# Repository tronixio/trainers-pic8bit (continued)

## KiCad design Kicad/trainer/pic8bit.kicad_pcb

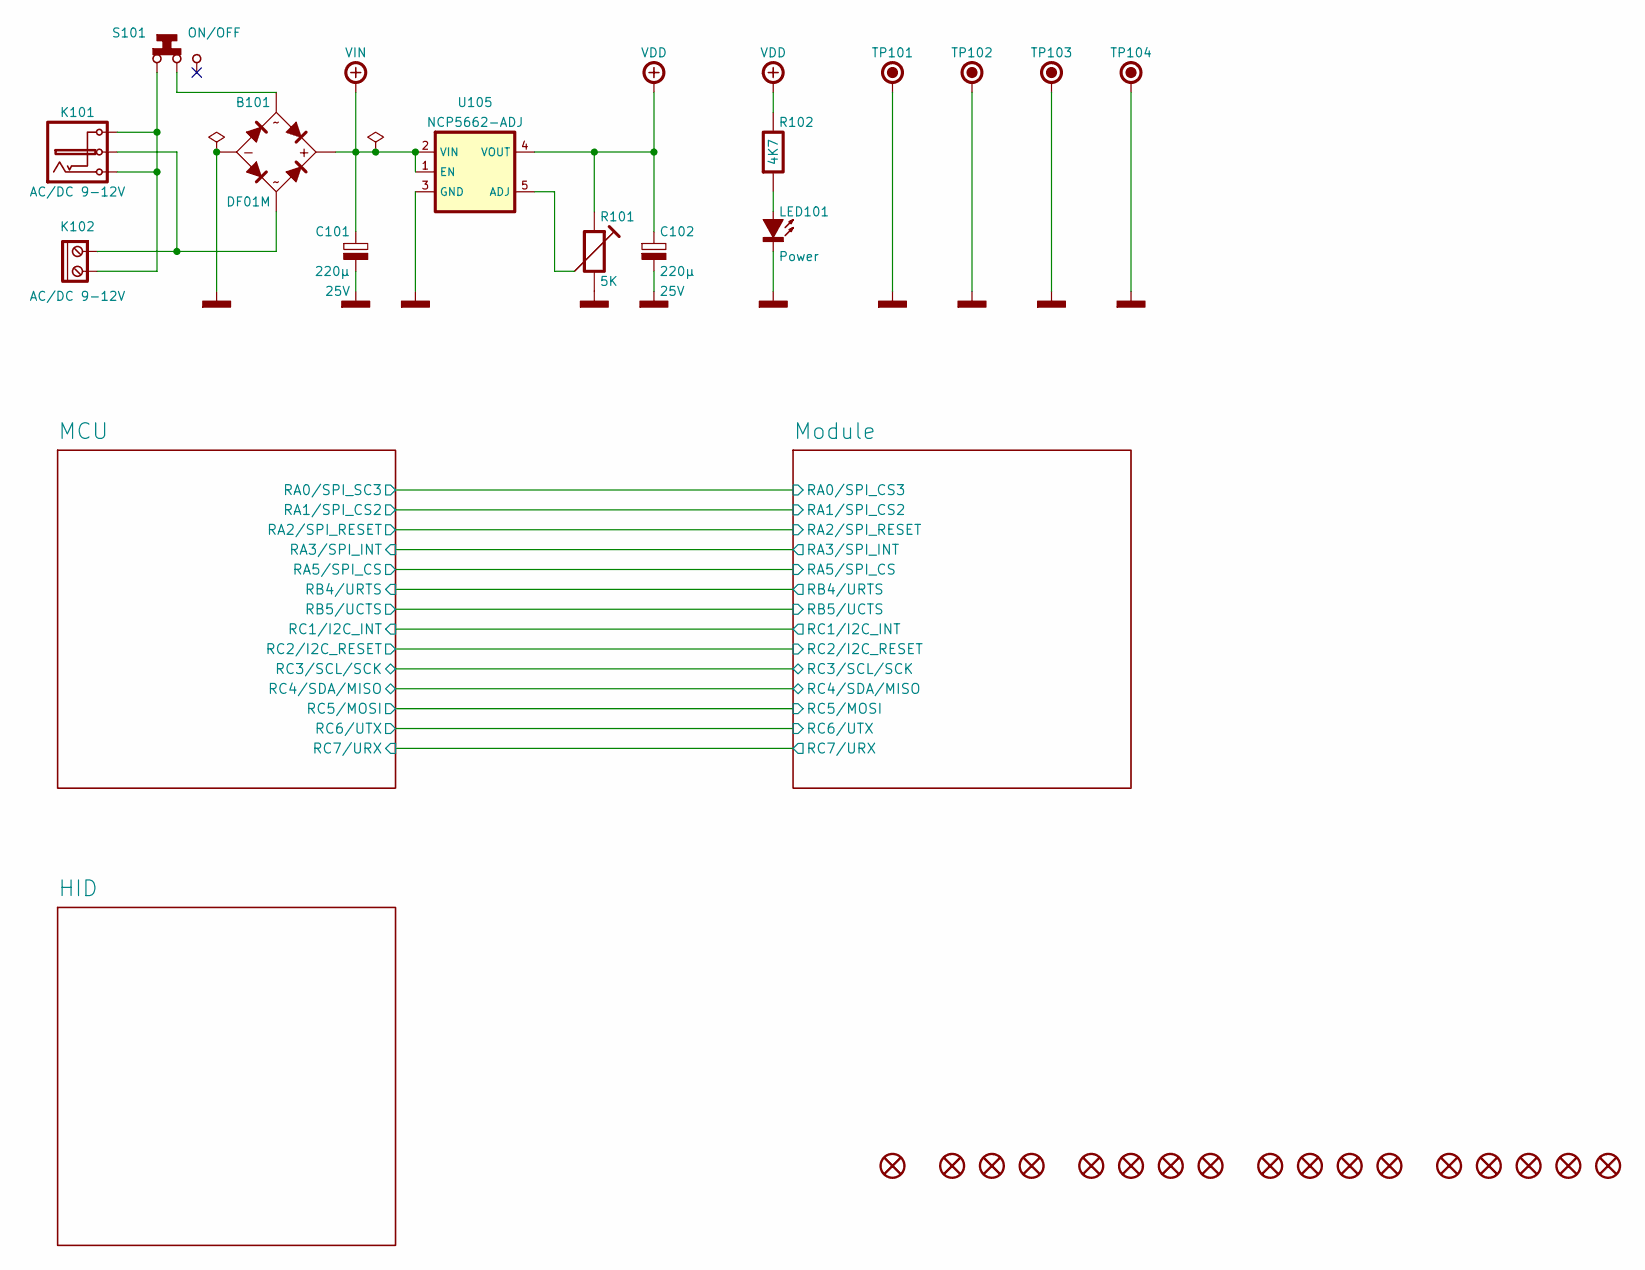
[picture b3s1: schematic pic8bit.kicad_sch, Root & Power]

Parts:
B101: DF01M; Mouser 512-DF01M
C101, C102: 220µ; CAPACITOR-ELECTROLYTIC-RADIAL-080-115-035; Voltage 25V; Tolerance 20%; Mouser 647-UVZ1E221MPD
H101, H102, H103, H104: HARWIN-JUMPER-0254-14MM-BLACK; HARWIN-M20-7680-7683; Mouser 855-M7682
JP101: HARWIN-JUMPER-0254-06MM-BLACK; HARWIN-M20-7580-7583; Mouser 855-M7582
JP102, JP103: HARWIN-JUMPER-0254-06MM-RED; HARWIN-M20-7580-7583; Mouser 855-M7581
K101: AC/DC 9-12V; SAMESKY-PJ-102AH; Mouser 490-PJ-102AH
K102: AC/DC 9-12V; SAMESKY-TB006-508-02BE; Mouser 490-TB006-508-02BE
K103: PE-450-4X6X-BLACK; PE-450-4X6X; Mouser 450-476
LED101: Power; LED-TH-ROUND-05MM; Mouser 604-WP7113ID
R101: 5K; TRIMMER-64W; Tolerance 10%; Mouser 594-64W502
R102: 4K7; RESISTOR-TH-1016; Tolerance 5%; Mouser 594-SFR2500004701JR5
S101: ON/OFF; CK-1101M2; Mouser 611-1101M2S3CQE2
TP101, TP102, TP103: GND; KEYSTONE-5006; Mouser 534-5006
TP104: GND; KEYSTONE-2000-3; Mouser 534-2000-3
U101, U102, U103, U104: KEYSTONE-24283; Mouser 534-24283
U105: NCP5662-ADJ; TO-263-5-TABPIN3; Mouser 863-NCP5662DSADJR4G
X101, X102, X103, X104, X105: 3M-SJ5376; Mouser 517-SJ5376

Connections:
unnamed: B101.3, K101.1, K102.1
unnamed: B101.4, S101.2
unnamed: K101.2, K101.3, K102.2, S101.1
unnamed: LED101.2 (A), R102.2
unnamed: R101.2, U105.5 (ADJ)
POWER-GND: B101.2, C101.2, C102.2, LED101.1 (C), R101.1, TP101.1, TP102.1, TP103.1, TP104.1, U105.3 (GND); also elsewhere on the board
POWER-VDD: C102.1, R101.3, R102.1, U105.4 (VOUT); also elsewhere on the board
POWER-VIN: B101.1, C101.1, U105.1 (EN), U105.2 (VIN); also elsewhere on the board

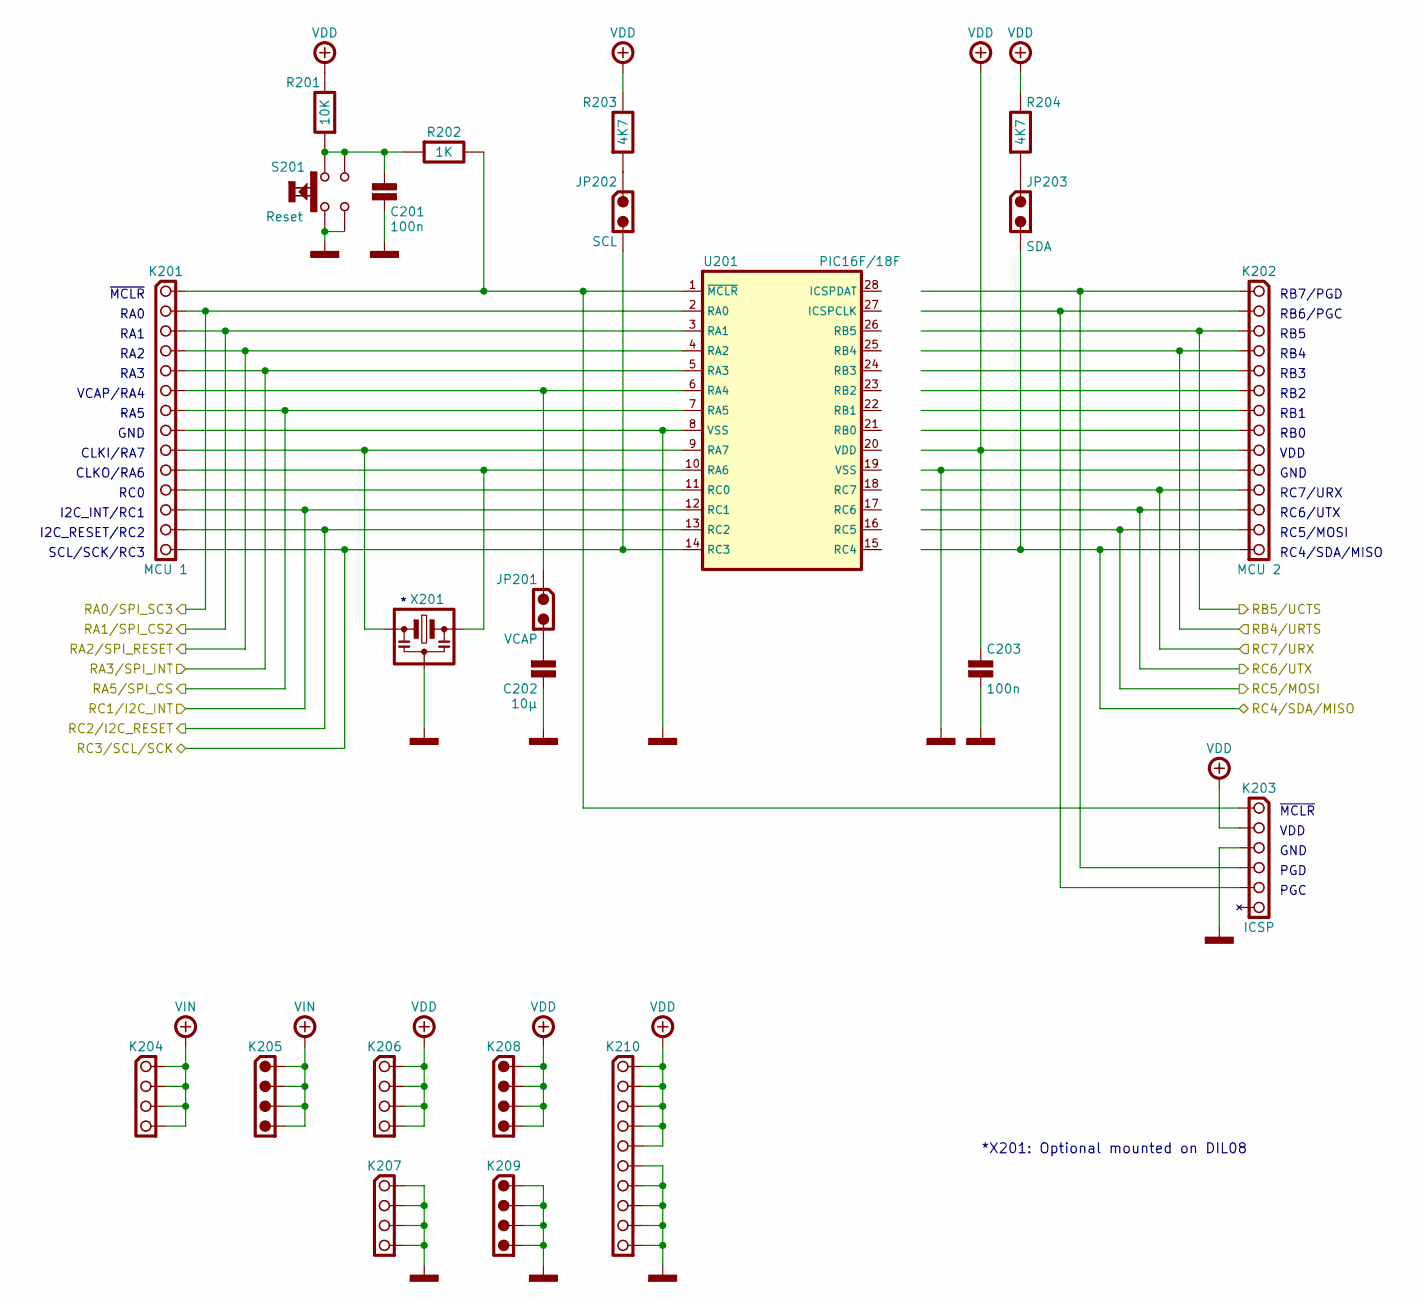
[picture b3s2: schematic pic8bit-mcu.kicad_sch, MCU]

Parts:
C201, C203: 100n; KEMET-C315; Tolerance 20%; Voltage 50V; Mouser 80-C315C104M5U
C202: 10µ; KEMET-C322; Tolerance 10%; Voltage 25V; Mouser 80-C322C106K3R
JP201: VCAP; HARWIN-M20-975024x; Mouser 855-M20-975024
JP202: SCL; HARWIN-M20-999024x; Mouser 855-M20-999024
JP203: SDA; HARWIN-M20-999024x; Mouser 855-M20-999024
K201: MCU 1; HARWIN-M20-782144x; Mouser 855-M20-782144
K202: MCU 2; HARWIN-M20-782144x; Mouser 855-M20-782144
K203: ICSP; SAMTEC-SSW-106-02-T-S-RA; Mouser 200-SSW10602TSRA
K204: VIN; HARWIN-M20-782044x; Mouser 855-M20-782044
K205: VIN; HARWIN-M20-999044x; Mouser 855-M20-999044
K206: VDD; HARWIN-M20-782044x; Mouser 855-M20-782044
K207: GND; HARWIN-M20-782044x; Mouser 855-M20-782044
K208: VDD; HARWIN-M20-999044x; Mouser 855-M20-999044
K209: GND; HARWIN-M20-999044x; Mouser 855-M20-999044
K210: VDD & GND; HARWIN-M20-782104x; Mouser 855-M20-782104
R201: 10K; RESISTOR-TH-1016; Tolerance 5%; Mouser 594-SFR2500001002JA5
R202: 1K; RESISTOR-TH-1016; Tolerance 5%; Mouser 594-SFR2500001001JR5
R203, R204: 4K7; RESISTOR-TH-1016; Tolerance 5%; Mouser 594-SFR2500004701JR5
S201: Reset; CK-KSA-TH; Mouser 611-KSA0M911LFT
U201: PIC16F/18F; DIP-28-W762; Mouser 579-PIC16F1778-I/SP
X201: XTAL-DIL08; DIP-08-W762-SOCKET; Mouser 575-144308

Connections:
/MCU/RA0/SPI_SC3: K201.2, U201.2 (RA0); also elsewhere on the board
/MCU/RA1/SPI_CS2: K201.3, U201.3 (RA1); also elsewhere on the board
/MCU/RA2/SPI_RESET: K201.4, U201.4 (RA2); also elsewhere on the board
/MCU/RA3/SPI_INT: K201.5, U201.5 (RA3); also elsewhere on the board
/MCU/RA5/SPI_CS: K201.7, U201.7 (RA5); also elsewhere on the board
/MCU/RB4/URTS: K202.4; also elsewhere on the board
/MCU/RB5/UCTS: K202.3; also elsewhere on the board
/MCU/RC1/I2C_INT: K201.12, U201.12 (RC1); also elsewhere on the board
/MCU/RC2/I2C_RESET: K201.13, U201.13 (RC2); also elsewhere on the board
/MCU/RC3/SCL/SCK: JP202.2, K201.14, U201.14 (RC3); also elsewhere on the board
/MCU/RC4/SDA/MISO: JP203.2, K202.14; also elsewhere on the board
/MCU/RC5/MOSI: K202.13; also elsewhere on the board
/MCU/RC6/UTX: K202.12; also elsewhere on the board
/MCU/RC7/URX: K202.11; also elsewhere on the board
unnamed: C201.1, R201.2, R202.2, S201.1, S201.2
unnamed: C202.1, JP201.2
unnamed: JP202.1, R203.2
unnamed: JP203.1, R204.2
unnamed: K201.1, K203.6 (~MCLR), R202.1, U201.1 (~MCLR)
unnamed: JP201.1, K201.6, U201.6 (RA4)
unnamed: K201.9, U201.9 (RA7), X201.3, X201.4
unnamed: K201.10, U201.10 (RA6), X201.5, X201.6
unnamed: K201.11, U201.11 (RC0)
unnamed: K202.1, K203.3 (PGD)
unnamed: K202.2, K203.2 (PGC)
POWER-GND: C201.2, C202.2, C203.2, K201.8, K202.10, K203.4 (GND), K207.1, K207.2, K207.3, K207.4, K209.1, K209.2, K209.3, K209.4, K210.6, K210.7, K210.8, K210.9, K210.10, S201.3, S201.4, U201.8 (VSS), X201.1, X201.2, X201.7, X201.8; also elsewhere on the board
POWER-VDD: C203.1, K202.9, K203.5 (VCC), K206.1, K206.2, K206.3, K206.4, K208.1, K208.2, K208.3, K208.4, K210.1, K210.2, K210.3, K210.4, K210.5, R201.1, R203.1, R204.1; also elsewhere on the board
POWER-VIN: K204.1, K204.2, K204.3, K204.4, K205.1, K205.2, K205.3, K205.4; also elsewhere on the board

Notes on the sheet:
RC6/UTX
VCAP/RA4
CLKI/RA7
VDD
PGC
RA3
RA0
RA2
RB6/PGC
RB5
*X201: Optional mounted on DIL08
RB7/PGD
~{MCLR}
GND
CLKO/RA6
PGD
RB4
RB2
RA1
RB3
RC5/MOSI
RA5
RB0
RC7/URX
RC4/SDA/MISO
I2C_INT/RC1
RC0
I2C_RESET/RC2
RB1
SCL/SCK/RC3

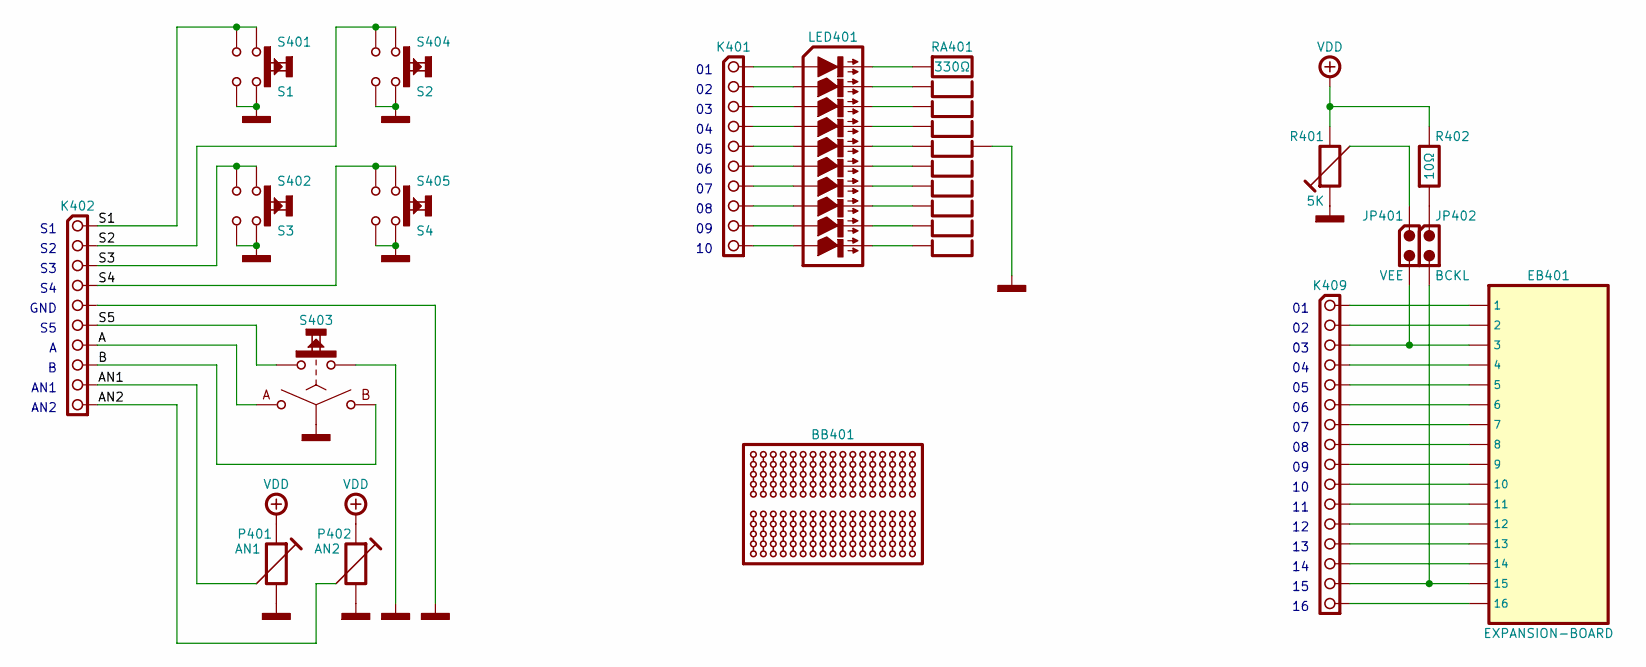
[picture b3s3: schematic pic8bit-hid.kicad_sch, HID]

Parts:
BB401: BREADBOARD-170; Mouser 854-BB170
EB401: EXPANSION-BOARD; TRONIXIO-EXPANSION-BOARD; Mouser 200-CES11601TS
JP401: VEE; HARWIN-M20-999024x; Mouser 855-M20-999024
JP402: BCKL; HARWIN-M20-999024x; Mouser 855-M20-999024
K401: LED ARRAY; HARWIN-M20-782104x; Mouser 855-M20-782104
K402: SWITCH, ENCODER & ANALOG; HARWIN-M20-782104x; Mouser 855-M20-782104
K409: EXPANSION BOARD; HARWIN-M20-782164x; Mouser 855-M20-782164
LED401: KINGBRIGHT-DC10EWA; KINGBRIGHT-DC; Mouser 604-DC-10EWA
P401: AN1; PIHER-PT10MV; Tolerance 20%; Mouser 531-PT10MV-10K
P402: AN2; PIHER-PT10MV; Tolerance 20%; Mouser 531-PT10MV-10K
R401: 5K; PIHER-PT10MV; Tolerance 20%; Mouser 531-PT10LV-5K
R402: 10Ω; RESISTOR-TH-1016; Tolerance 5%; Mouser 594-5043EM10R00J
RA401: 330Ω; BOURNS-4611X; Tolerance 2%; Mouser 652-4611X-1LF-330
S401: S1; CK-KSA-TH; Mouser 611-KSA0M911LFT
S402: S3; CK-KSA-TH; Mouser 611-KSA0M911LFT
S403: BOURNS-PEC12R-24DENTS; BOURNS-PEC12R-SWITCH; Mouser 652-PEC12R-4215F-S24
S404: S2; CK-KSA-TH; Mouser 611-KSA0M911LFT
S405: S4; CK-KSA-TH; Mouser 611-KSA0M911LFT

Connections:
/HID/A: K402.7, S403.1 (A)
/HID/AN1: K402.9, P401.2
/HID/AN2: K402.10, P402.2
/HID/B: K402.8, S403.3 (B)
/HID/S1: K402.1, S401.1, S401.2
/HID/S2: K402.2, S404.1, S404.2
/HID/S3: K402.3, S402.1, S402.2
/HID/S4: K402.4, S405.1, S405.2
/HID/S5: K402.6, S403.5
unnamed: JP401.1, R401.2
unnamed: JP402.1, R402.2
unnamed: K401.1, LED401.1 (A1)
unnamed: K401.2, LED401.2 (A2)
unnamed: K401.3, LED401.3 (A3)
unnamed: K401.4, LED401.4 (A4)
unnamed: K401.5, LED401.5 (A5)
unnamed: K401.6, LED401.6 (A6)
unnamed: K401.7, LED401.7 (A7)
unnamed: K401.8, LED401.8 (A8)
unnamed: K401.9, LED401.9 (A9)
unnamed: K401.10, LED401.10 (A10)
unnamed: EB401.1, K409.1
unnamed: EB401.2, K409.2
unnamed: EB401.3, JP401.2, K409.3
unnamed: EB401.4, K409.4
unnamed: EB401.5, K409.5
unnamed: EB401.6, K409.6
unnamed: EB401.7, K409.7
unnamed: EB401.8, K409.8
unnamed: EB401.9, K409.9
unnamed: EB401.10, K409.10
unnamed: EB401.11, K409.11
unnamed: EB401.12, K409.12
unnamed: EB401.13, K409.13
unnamed: EB401.14, K409.14
unnamed: EB401.15, JP402.2, K409.15
unnamed: EB401.16, K409.16
unnamed: LED401.20 (C1), RA401.2
unnamed: LED401.19 (C2), RA401.3
unnamed: LED401.18 (C3), RA401.4
unnamed: LED401.17 (C4), RA401.5
unnamed: LED401.16 (C5), RA401.6
unnamed: LED401.15 (C6), RA401.7
unnamed: LED401.14 (C7), RA401.8
unnamed: LED401.13 (C8), RA401.9
unnamed: LED401.12 (C9), RA401.10
unnamed: LED401.11 (C10), RA401.11
POWER-GND: K402.5, P401.1, P402.1, R401.3, RA401.1, S401.3, S401.4, S402.3, S402.4, S403.2 (C), S403.4, S404.3, S404.4, S405.3, S405.4; also elsewhere on the board
POWER-VDD: P401.3, P402.3, R401.1, R402.1; also elsewhere on the board

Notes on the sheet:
AN2
GND
AN1

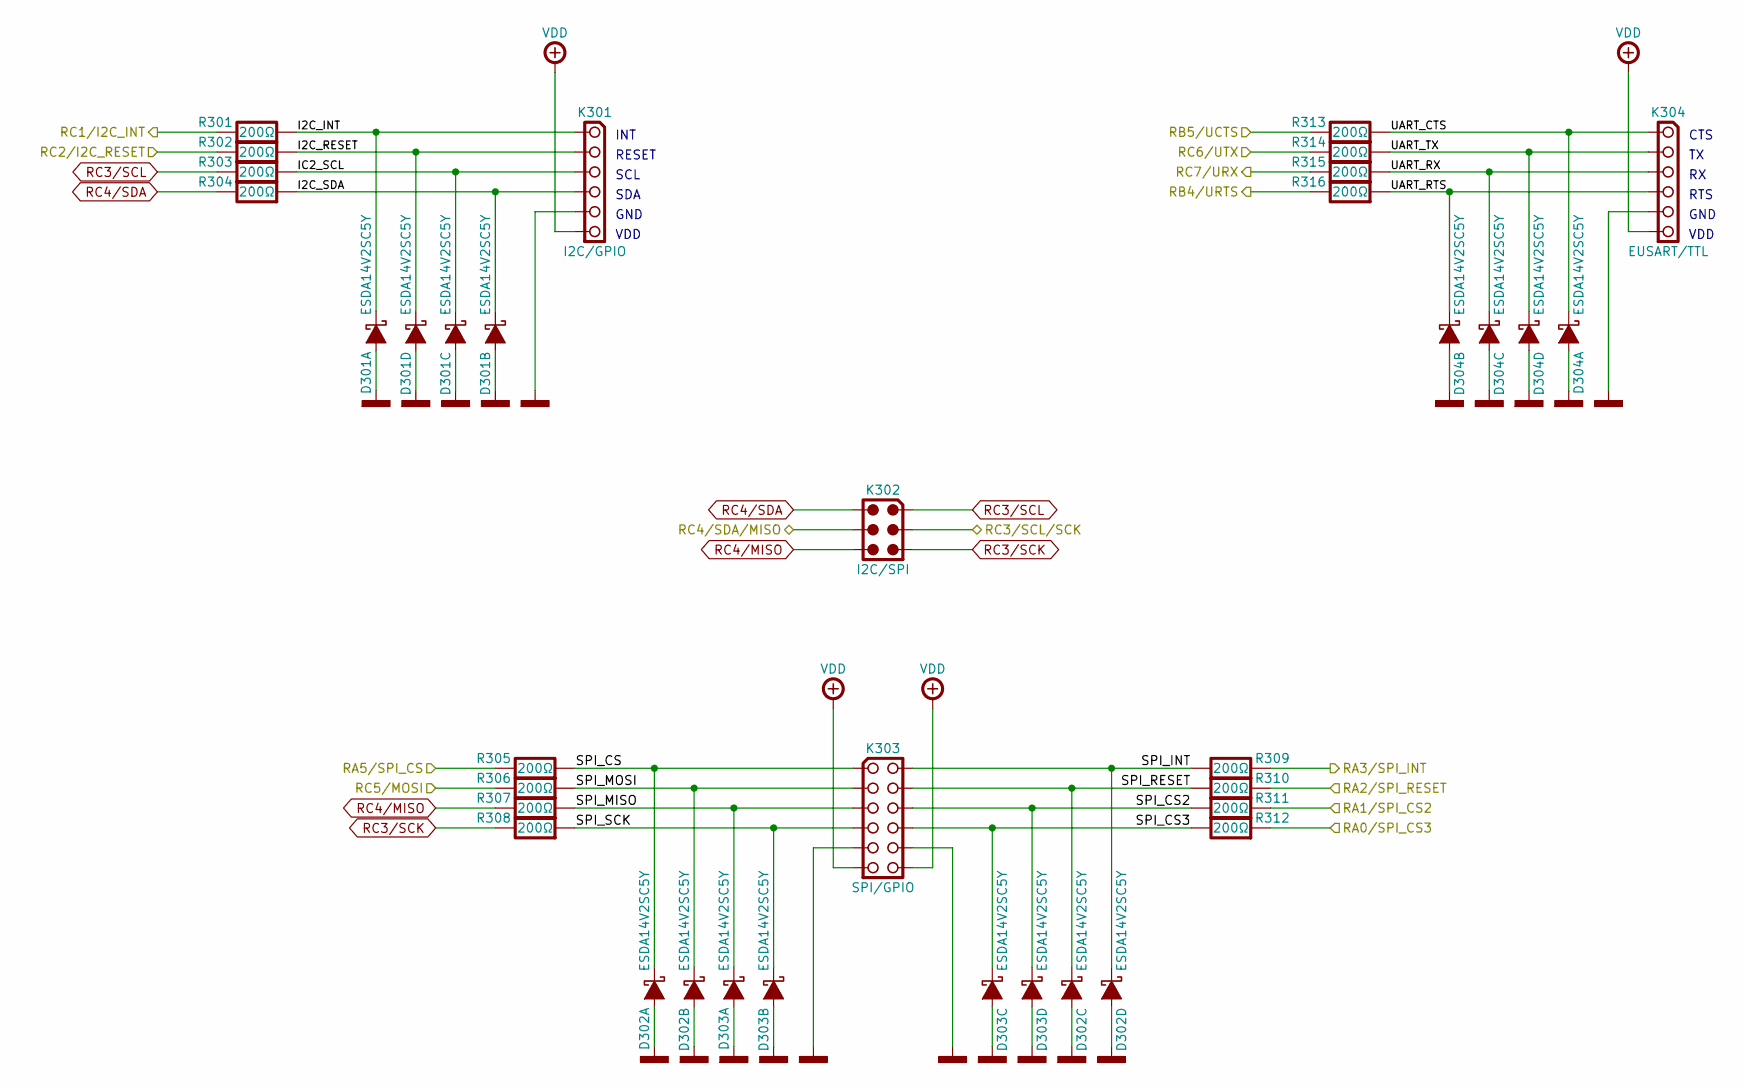
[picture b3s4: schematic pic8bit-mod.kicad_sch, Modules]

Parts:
D301, D302, D303, D304: ESDA14V2SC5Y; SOT-23-5; Mouser 511-ESDA14V2SC5Y
K301: I2C/GPIO; SAMTEC-SSW-106-02-T-S-RA; Mouser 200-SSW10603TSRA
K302: I2C/SPI; HARWIN-M20-974034x; Mouser 855-M20-974034
K303: SPI/GPIO; SAMTEC-SSW-106-02-T-D-RA; Mouser 200-SSW10602TDRA
K304: EUSART/TTL; SAMTEC-SSW-106-02-T-S-RA; Mouser 200-SSW10603TSRA
R301, R302, R303, R304, R305, R306, R307, R308, R309, R310, R311, R312, R313, R314, R315, R316: 200Ω; RESISTOR-SMD-1206; Tolerance 5%; Mouser 660-RK73B2BTTDD201J

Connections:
/MCU/RA0/SPI_SC3: R312.2; also elsewhere on the board
/MCU/RA1/SPI_CS2: R311.2; also elsewhere on the board
/MCU/RA2/SPI_RESET: R310.2; also elsewhere on the board
/MCU/RA3/SPI_INT: R309.2; also elsewhere on the board
/MCU/RA5/SPI_CS: R305.1; also elsewhere on the board
/MCU/RB4/URTS: R316.1; also elsewhere on the board
/MCU/RB5/UCTS: R313.1; also elsewhere on the board
/MCU/RC1/I2C_INT: R301.1; also elsewhere on the board
/MCU/RC2/I2C_RESET: R302.1; also elsewhere on the board
/MCU/RC3/SCL/SCK: K302.3; also elsewhere on the board
/MCU/RC4/SDA/MISO: K302.4; also elsewhere on the board
/MCU/RC5/MOSI: R306.1; also elsewhere on the board
/MCU/RC6/UTX: R314.1; also elsewhere on the board
/MCU/RC7/URX: R315.1; also elsewhere on the board
/Module/I2C_INT: D301.1 (C), K301.1, R301.2
/Module/I2C_RESET: D301.5 (C), K301.2, R302.2
/Module/I2C_SDA: D301.3 (C), K301.4, R304.2
/Module/IC2_SCL: D301.4 (C), K301.3, R303.2
/Module/SPI_CS: D302.1 (C), K303.1, R305.2
/Module/SPI_CS2: D303.5 (C), K303.6, R311.1
/Module/SPI_CS3: D303.4 (C), K303.8, R312.1
/Module/SPI_INT: D302.5 (C), K303.2, R309.1
/Module/SPI_MISO: D303.1 (C), K303.5, R307.2
/Module/SPI_MOSI: D302.3 (C), K303.3, R306.2
/Module/SPI_RESET: D302.4 (C), K303.4, R310.1
/Module/SPI_SCK: D303.3 (C), K303.7, R308.2
/Module/UART_CTS: D304.1 (C), K304.1, R313.2
/Module/UART_RTS: D304.3 (C), K304.4, R316.2
/Module/UART_RX: D304.4 (C), K304.3, R315.2
/Module/UART_TX: D304.5 (C), K304.2, R314.2
POWER-GND: D301.2 (A), D302.2 (A), D303.2 (A), D304.2 (A), K301.5, K303.9, K303.10, K304.5; also elsewhere on the board
POWER-VDD: K301.6, K303.11, K303.12, K304.6; also elsewhere on the board
RC3/SCK: K302.5, R308.1
RC3/SCL: K302.1, R303.1
RC4/MISO: K302.6, R307.1
RC4/SDA: K302.2, R304.1

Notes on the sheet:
INT
VDD
SCL
GND
SDA
CTS
RESET
RTS

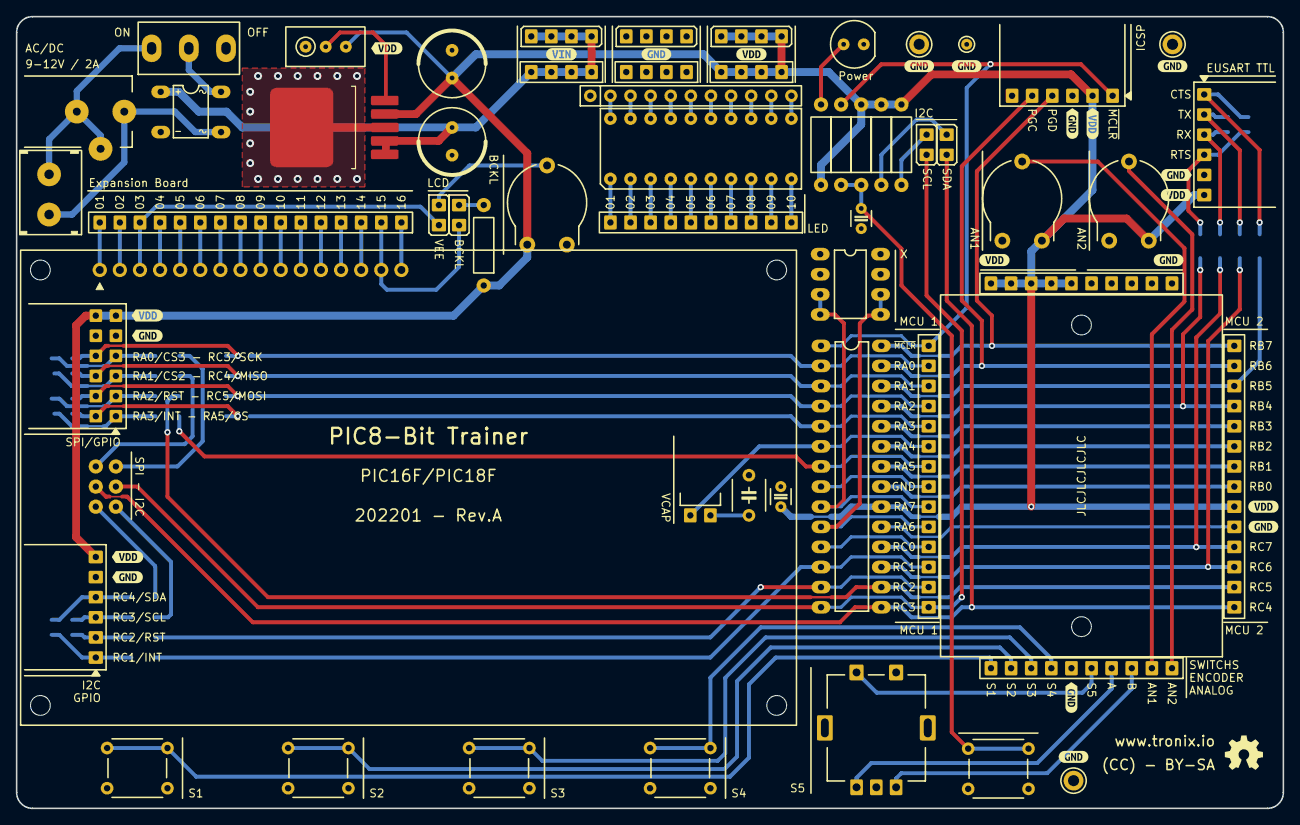
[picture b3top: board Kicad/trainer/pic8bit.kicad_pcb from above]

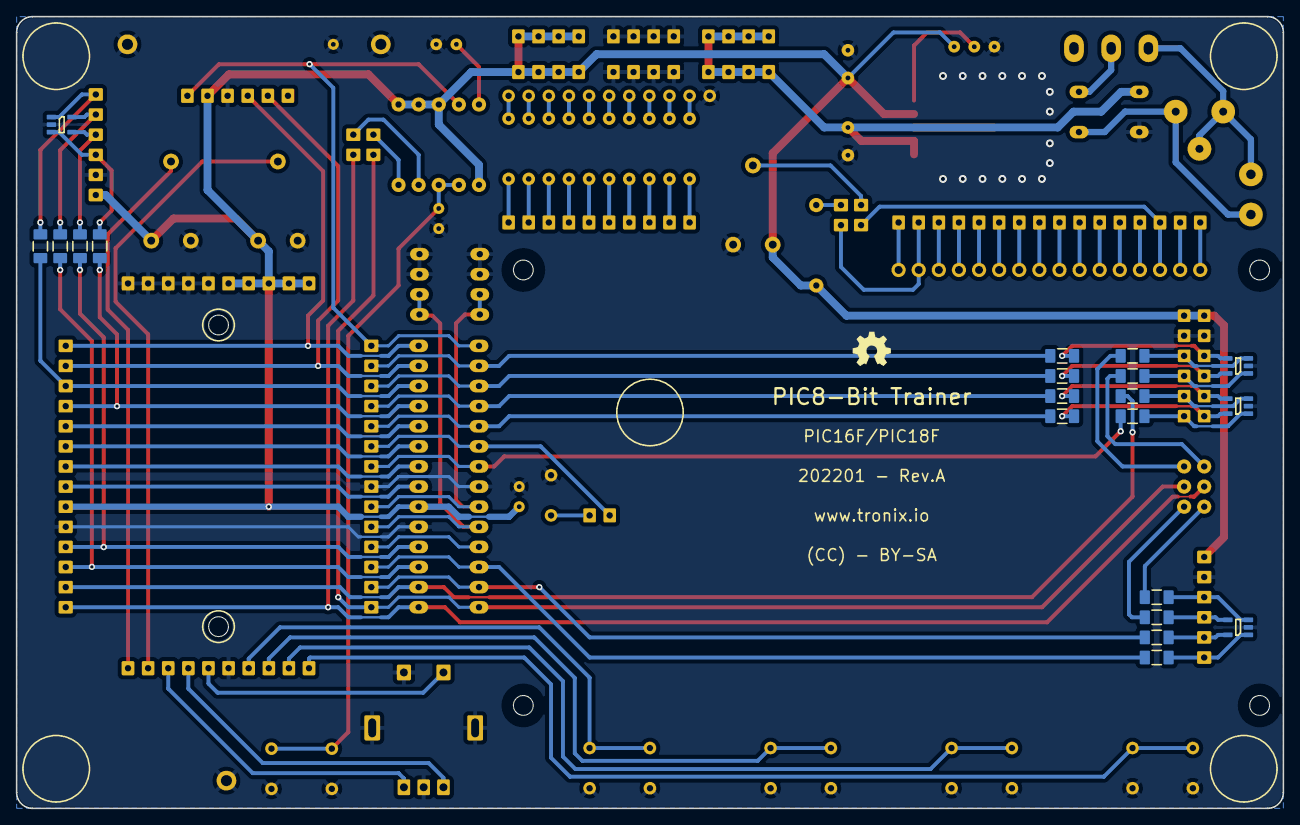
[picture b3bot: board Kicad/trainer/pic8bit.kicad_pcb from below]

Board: 2 copper layers, 160.0 x 100.0 mm, 117 parts (25 on the bottom side), 100 nets.

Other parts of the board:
kibuzzard-65F605A7: G***; kibuzzard-65F605A7
kibuzzard-65F605B3: G***; kibuzzard-65F605B3
kibuzzard-65F605BE: G***; kibuzzard-65F605BE
kibuzzard-65F605CA: G***; kibuzzard-65F605CA
kibuzzard-65F605D7: G***; kibuzzard-65F605D7
kibuzzard-65F605E6: G***; kibuzzard-65F605E6
kibuzzard-65F605F2: G***; kibuzzard-65F605F2
kibuzzard-65F6052C: G***; kibuzzard-65F6052C
kibuzzard-65F6056F: G***; kibuzzard-65F6056F
kibuzzard-65F6059C: G***; kibuzzard-65F6059C
kibuzzard-65F60515: G***; kibuzzard-65F60515
kibuzzard-65F60520: G***; kibuzzard-65F60520
kibuzzard-65F60537: G***; kibuzzard-65F60537
kibuzzard-65F60546: G***; kibuzzard-65F60546
kibuzzard-65F60553: G***; kibuzzard-65F60553
kibuzzard-65F60562: G***; kibuzzard-65F60562
kibuzzard-65F60578: G***; kibuzzard-65F60578
kibuzzard-65F60585: G***; kibuzzard-65F60585
kibuzzard-65F60590: G***; kibuzzard-65F60590
kibuzzard-65F60603: G***; kibuzzard-65F60603
kibuzzard-65F60610: G***; kibuzzard-65F60610

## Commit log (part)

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2022-01-10 Add Kicad
2022-01-10 Add Features
2022-01-10 Add Readme
2022-01-17 Update Nano
2022-01-17 Update Mini
2022-01-17 Add Trainer
2022-01-17 Update Trainer
2022-04-24 Update DAC5
2022-04-24 Update GPIO
2022-05-07 Add Firmwares
2022-05-21 Upadte
2023-01-18 Update pic8bit trainer
2023-01-29 PIC16F18856 DOGM081
2024-03-16 Update Nano Kicad 8
2024-03-16 Update Mini Kicad 8
2024-03-16 Update Trainer Kicad 8
2024-03-17 Update Nano & Mini
2026-04-24 Mini
